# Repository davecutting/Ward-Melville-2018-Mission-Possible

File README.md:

# WMHS Mission Possible 2018 # 

This repository contains code and circuit board design files for Ward Melville High School's A team Mission Prossible device in the 2017-2018 season. All work represented here is the original work of David Cutting.

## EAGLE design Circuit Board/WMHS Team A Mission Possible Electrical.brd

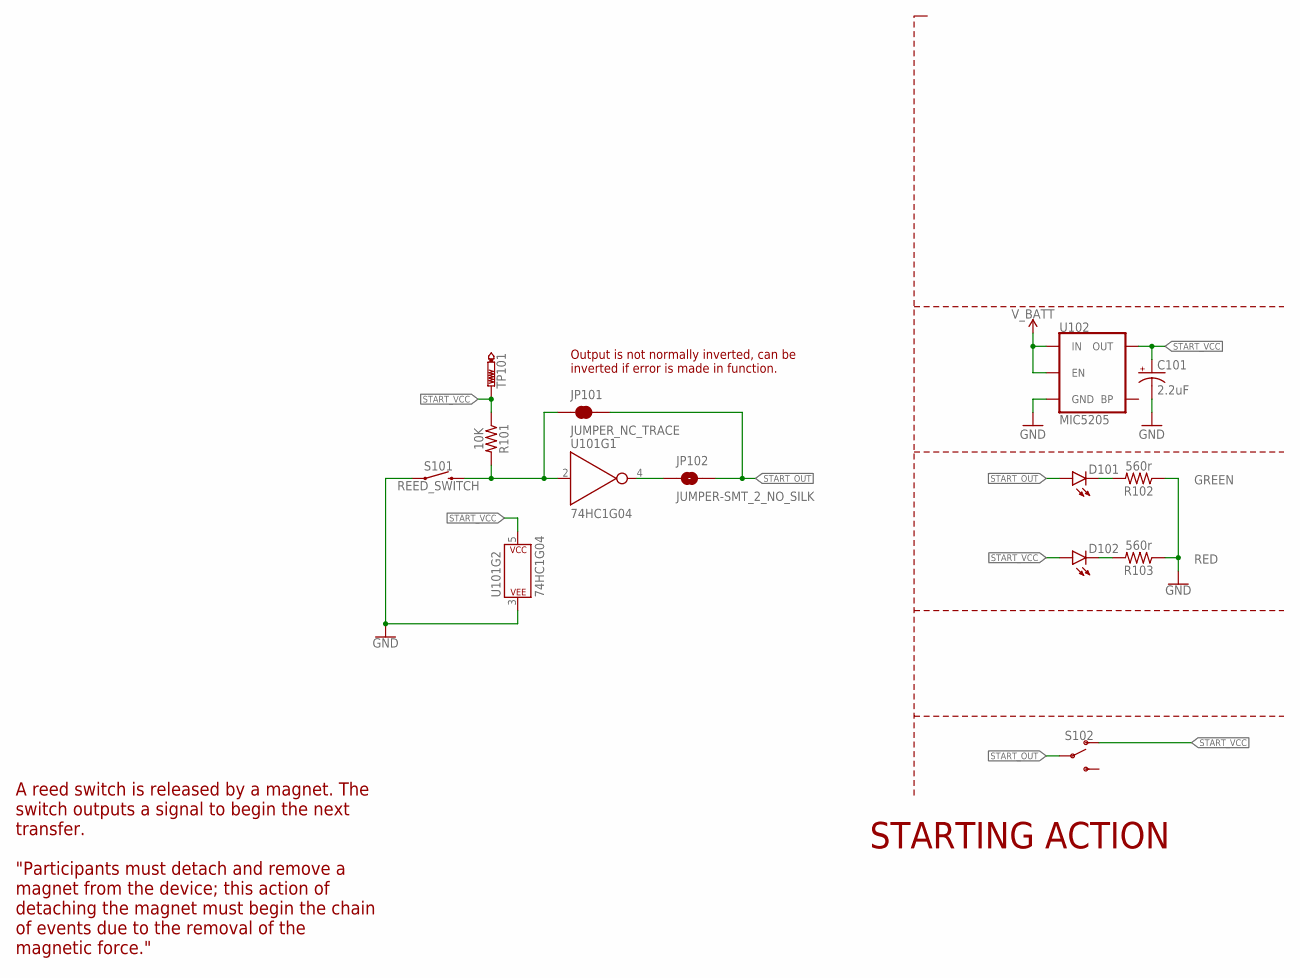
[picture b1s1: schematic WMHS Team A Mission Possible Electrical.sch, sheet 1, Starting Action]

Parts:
C101: 2.2uF; EIA3216
D101: GREEN; LED-0603
D102: RED; LED-0603
JP101: JUMPER_NC_TRACE; SMT-JUMPER_2_NC_TRACE_SILK
JP102: JUMPER-SMT_2_NO_SILK; SMT-JUMPER_2_NO_SILK
R101: 10K; 0603
R102, R103: 560r; 0603
S101: REED_SWITCH; AXIAL_GULLWING_REED
S102: SWITCH-SPDT-SMD-AYZ0202; SWITCH_DPDT_SMD_AYZ0202
TP101: PTR1TP20R; TP20R
U101: 74HC1G04; SOT353
U102: MIC5205; SOT23-5

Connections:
GND: C101.-, R102.1, R103.1, S101.P$1 (1), U101.3 (P$V-), U102.2 (GND); also elsewhere on the board
unnamed: JP102.1, U101.4 (Y)
unnamed: JP101.1, R101.2, S101.P$2 (2), U101.2 (A)
unnamed: D102.C, R103.2
unnamed: D101.C, R102.2
START_OUT: D101.A, JP101.2, JP102.2, S102.2; also elsewhere on the board
START_VCC: C101.+, D102.A, R101.1, S102.1 (O), TP101.TP, U101.5 (P$V+), U102.5 (OUT)
V_BATT: U102.1 (IN), U102.3 (EN); also elsewhere on the board

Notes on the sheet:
STARTING ACTION
"Participants must detach and remove a magnet from the device; this action of detaching the magnet must begin the chain of events due to the removal of the magnetic force."
A reed switch is released by a magnet. The switch outputs a signal to begin the next transfer.
Output is not normally inverted, can be inverted if error is made in function.

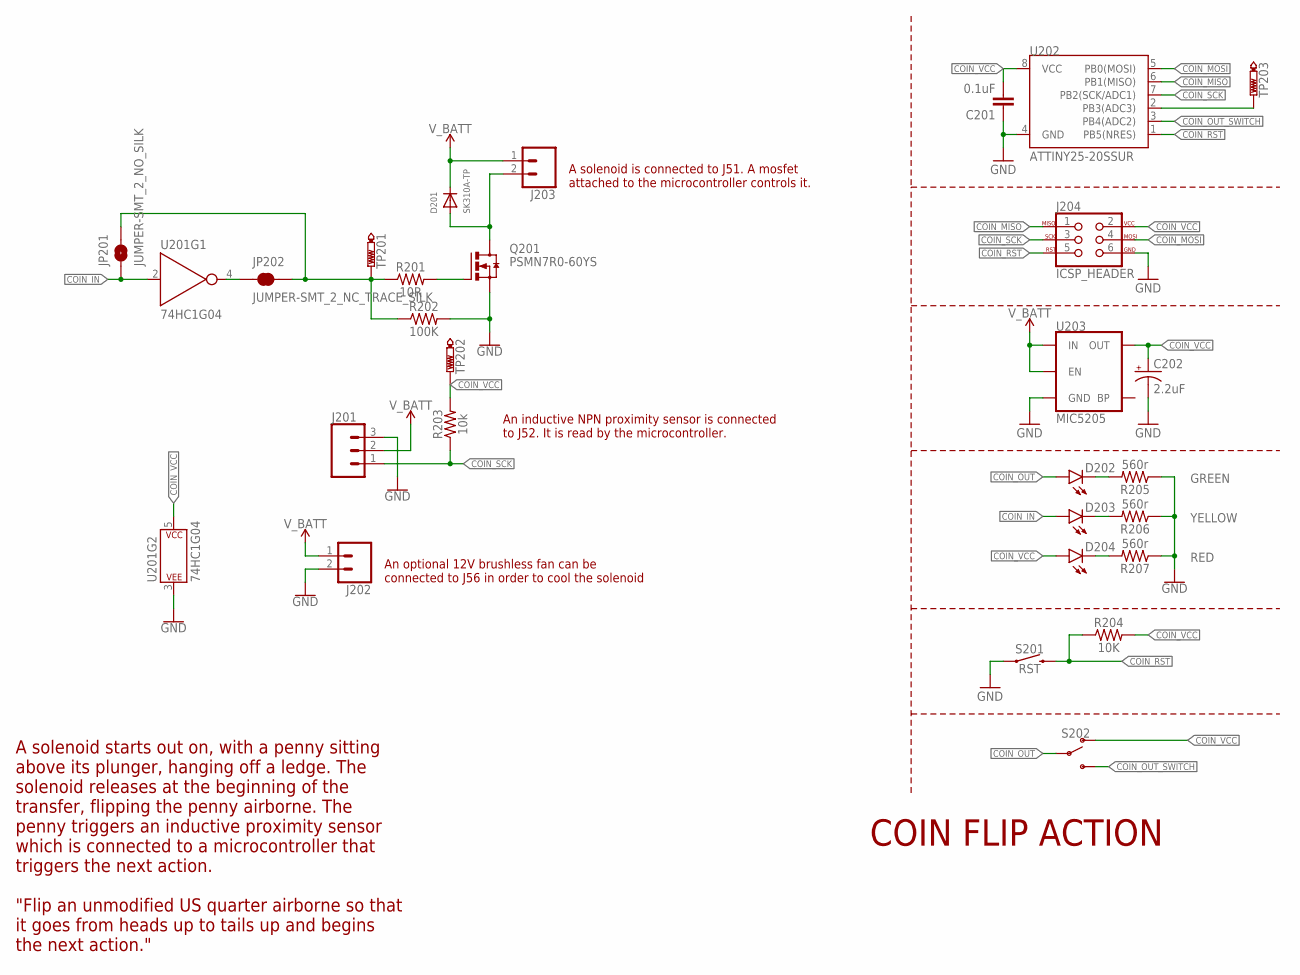
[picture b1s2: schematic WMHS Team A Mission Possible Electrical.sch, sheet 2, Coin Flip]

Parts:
C201: 0.1uF; 0603
C202: 2.2uF; EIA3216
D201: SK310A-TP; SMADIODE
D202: GREEN; LED-0603
D203: YELLOW; LED-0603
D204: RED; LED-0603
J201: CONN_03LOCK; 1X03_LOCK
J202: CONN_02LOCK; 1X02_LOCK
J203: CONN_023.5MM_LOCK; SCREWTERMINAL-3.5MM-2_LOCK
J204: ICSP_HEADER; 2X3
JP201: JUMPER-SMT_2_NO_SILK; SMT-JUMPER_2_NO_SILK
JP202: JUMPER-SMT_2_NC_TRACE_SILK; SMT-JUMPER_2_NC_TRACE_SILK
Q201: PSMN7R0-60YS; SOT669
R201: 10R; 0603
R202: 100K; 0603
R203: 10k; 0603
R204: 10K; 0603
R205, R206, R207: 560r; 0603
S201: RST; TACTILE_SWITCH_SMD_5.2MM
S202: SWITCH-SPDT-SMD-AYZ0202; SWITCH_DPDT_SMD_AYZ0202
TP201, TP202, TP203: PTR1TP20R; TP20R
U201: 74HC1G04; SOT353
U202: ATTINY25-20SSUR; SOIC8
U203: MIC5205; SOT23-5

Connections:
COIN_IN: D203.A, JP201.1, U201.2 (A); also elsewhere on the board
COIN_MISO: J204.1, U202.6 (PB1(MISO))
COIN_MOSI: J204.4, U202.5 (PB0(MOSI))
COIN_OUT: D202.A, S202.2; also elsewhere on the board
COIN_OUT_SWITCH: S202.3 (S), U202.3 (PB4(ADC2))
COIN_RST: J204.5, R204.1, S201.3 (2), S201.4 (2), U202.1 (PB5(NRES))
COIN_SCK: J201.1, J204.3, R203.1, U202.7 (PB2(SCK/ADC1))
COIN_VCC: C201.2, C202.+, D204.A, J204.2, R203.2, R204.2, S202.1 (O), TP202.TP, U201.5 (P$V+), U202.8 (VCC), U203.5 (OUT)
GND: C201.1, C202.-, J201.3, J202.2, J204.6, Q201.1 (S), Q201.2 (S), Q201.3 (S), R202.2, R205.1, R206.1, R207.1, S201.1, S201.2 (1), U201.3 (P$V-), U202.4 (GND), U203.2 (GND); also elsewhere on the board
unnamed: TP203.TP, U202.2 (PB3(ADC3))
unnamed: JP201.2, JP202.2, R201.1, R202.1, TP201.TP
unnamed: JP202.1, U201.4 (Y)
unnamed: Q201.4 (G), R201.2
unnamed: D201.A, J203.2, Q201.MB (D)
unnamed: D204.C, R207.2
unnamed: D203.C, R206.2
unnamed: D202.C, R205.2
V_BATT: D201.C, J201.2, J202.1, J203.1, U203.1 (IN), U203.3 (EN); also elsewhere on the board

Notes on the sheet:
COIN FLIP ACTION
"Flip an unmodified US quarter airborne so that it goes from heads up to tails up and begins the next action."
A solenoid is connected to J51. A mosfet attached to the microcontroller controls it.
An inductive NPN proximity sensor is connected to J52. It is read by the microcontroller.
An optional 12V brushless fan can be connected to J56 in order to cool the solenoid
A solenoid starts out on, with a penny sitting above its plunger, hanging off a ledge. The solenoid releases at the beginning of the transfer, flipping the penny airborne. The penny triggers an inductive proximity sensor which is connected to a microcontroller that triggers the next action.

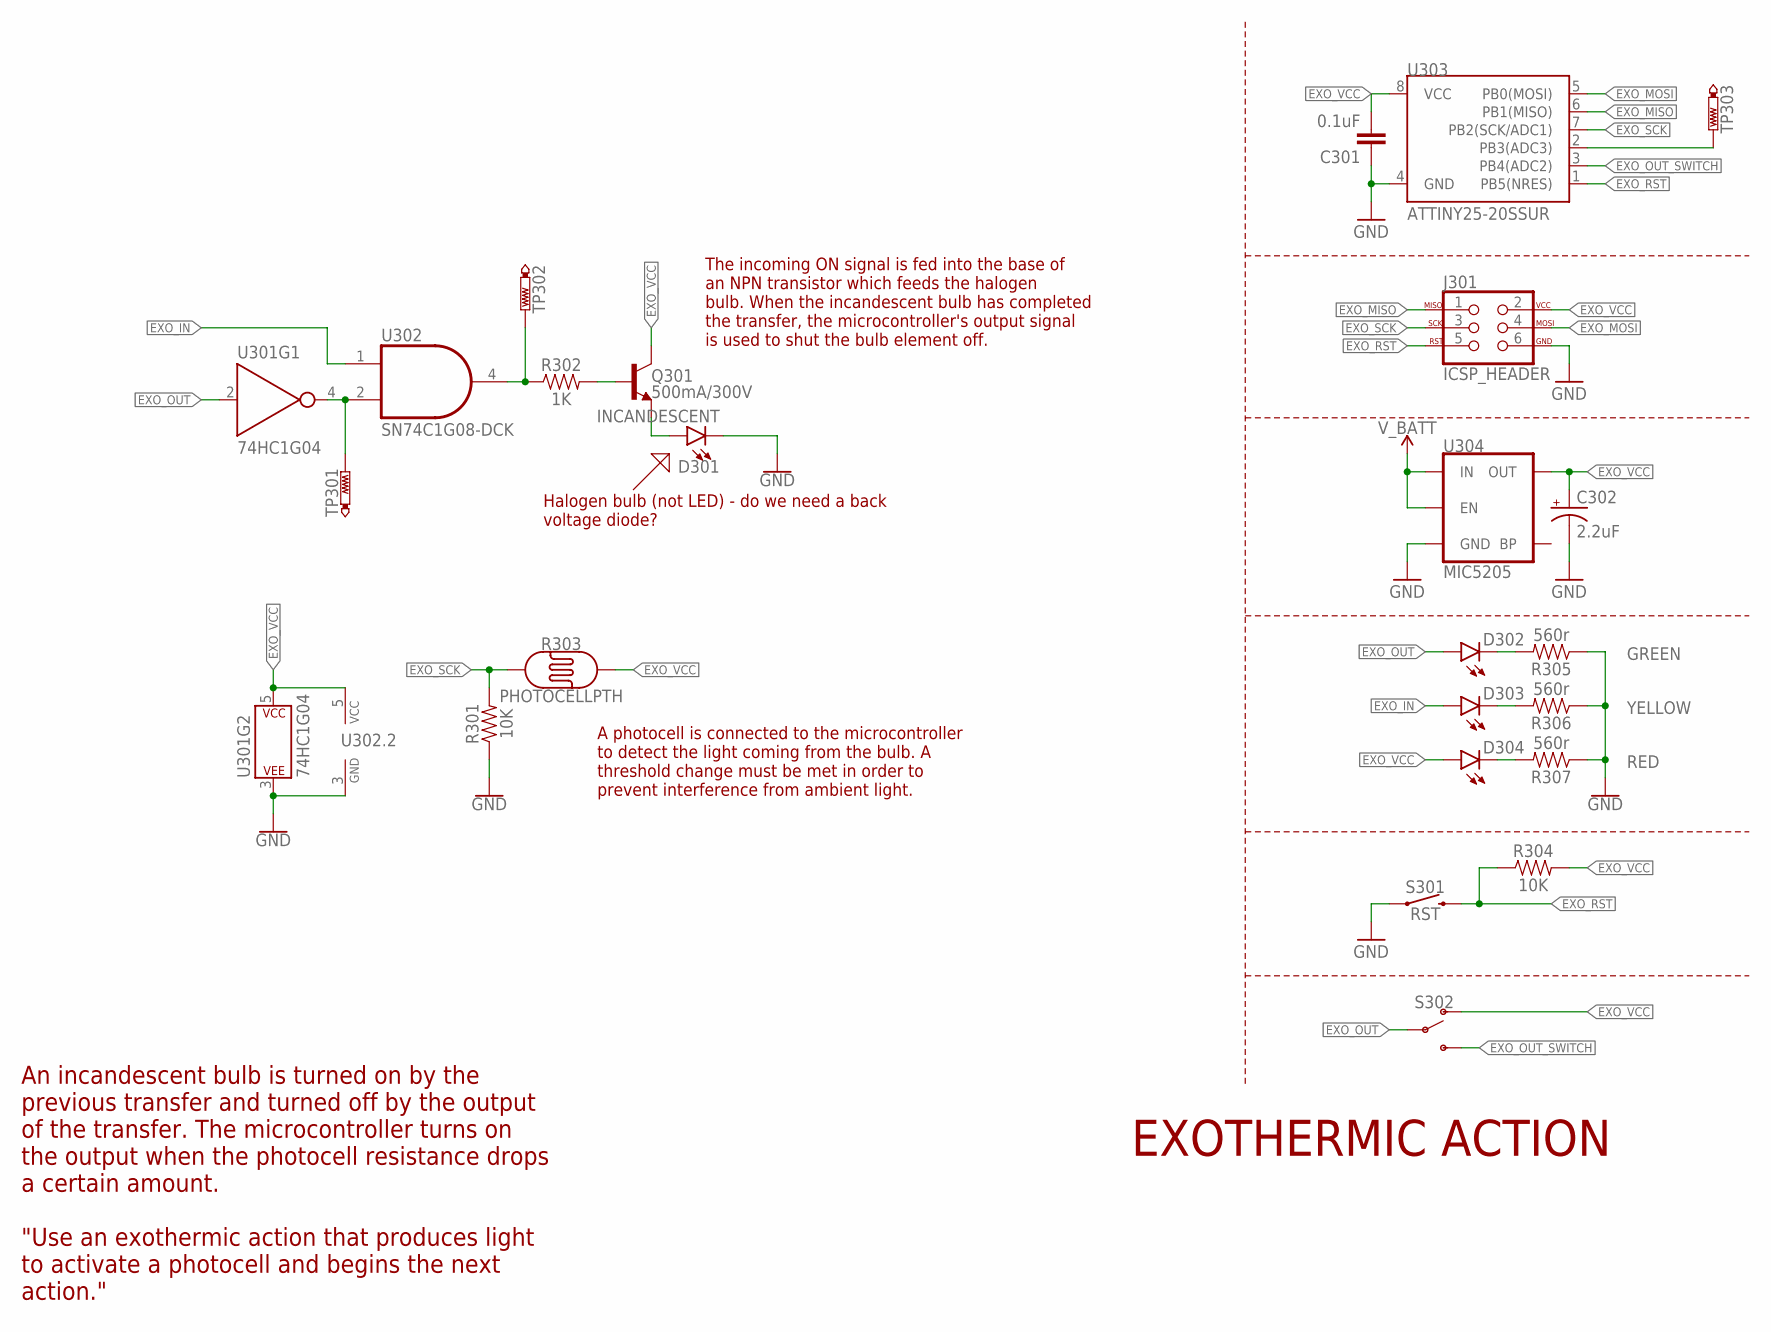
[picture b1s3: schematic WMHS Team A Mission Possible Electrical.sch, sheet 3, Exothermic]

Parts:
C301: 0.1uF; 0603
C302: 2.2uF; EIA3216
D301: INCANDESCENT; LED_3MM
D302: GREEN; LED-0603
D303: YELLOW; LED-0603
D304: RED; LED-0603
J301: ICSP_HEADER; 2X3
Q301: 500mA/300V; SOT23-3
R301, R304: 10K; 0603
R302: 1K; 0603
R303: PHOTOCELLPTH; PHOTOCELL
R305, R306, R307: 560r; 0603
S301: RST; TACTILE_SWITCH_SMD_5.2MM
S302: SWITCH-SPDT-SMD-AYZ0202; SWITCH_DPDT_SMD_AYZ0202
TP301, TP302, TP303: PTR1TP20R; TP20R
U301: 74HC1G04; SOT353
U302: SN74C1G08-DCK; SC-70-5
U303: ATTINY25-20SSUR; SOIC8
U304: MIC5205; SOT23-5

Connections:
EXO_IN: D303.A, U302.1 (A); also elsewhere on the board
EXO_MISO: J301.1, U303.6 (PB1(MISO))
EXO_MOSI: J301.4, U303.5 (PB0(MOSI))
EXO_OUT: D302.A, S302.2, U301.2 (A); also elsewhere on the board
EXO_OUT_SWITCH: S302.3 (S), U303.3 (PB4(ADC2))
EXO_RST: J301.5, R304.1, S301.3 (2), S301.4 (2), U303.1 (PB5(NRES))
EXO_SCK: J301.3, R301.2, R303.1, U303.7 (PB2(SCK/ADC1))
EXO_VCC: C301.2, C302.+, D304.A, J301.2, Q301.3 (C), R303.2, R304.2, S302.1 (O), U301.5 (P$V+), U302.5 (VCC), U303.8 (VCC), U304.5 (OUT)
GND: C301.1, C302.-, D301.K (C), J301.6, R301.1, R305.1, R306.1, R307.1, S301.1, S301.2 (1), U301.3 (P$V-), U302.3 (GND), U303.4 (GND), U304.2 (GND); also elsewhere on the board
unnamed: R302.1, TP302.TP, U302.4 (Y)
unnamed: TP301.TP, U301.4 (Y), U302.2 (B)
unnamed: TP303.TP, U303.2 (PB3(ADC3))
unnamed: Q301.1 (B), R302.2
unnamed: D301.A, Q301.2 (E)
unnamed: D304.C, R307.2
unnamed: D303.C, R306.2
unnamed: D302.C, R305.2
V_BATT: U304.1 (IN), U304.3 (EN); also elsewhere on the board

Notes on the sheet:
EXOTHERMIC ACTION
"Use an exothermic action that produces light to activate a photocell and begins the next action."
Halogen bulb (not LED) - do we need a back voltage diode?
The incoming ON signal is fed into the base of an NPN transistor which feeds the halogen bulb. When the incandescent bulb has completed the transfer, the microcontroller's output signal is used to shut the bulb element off.
A photocell is connected to the microcontroller to detect the light coming from the bulb. A threshold change must be met in order to prevent interference from ambient light.
An incandescent bulb is turned on by the previous transfer and turned off by the output of the transfer. The microcontroller turns on the output when the photocell resistance drops a certain amount.

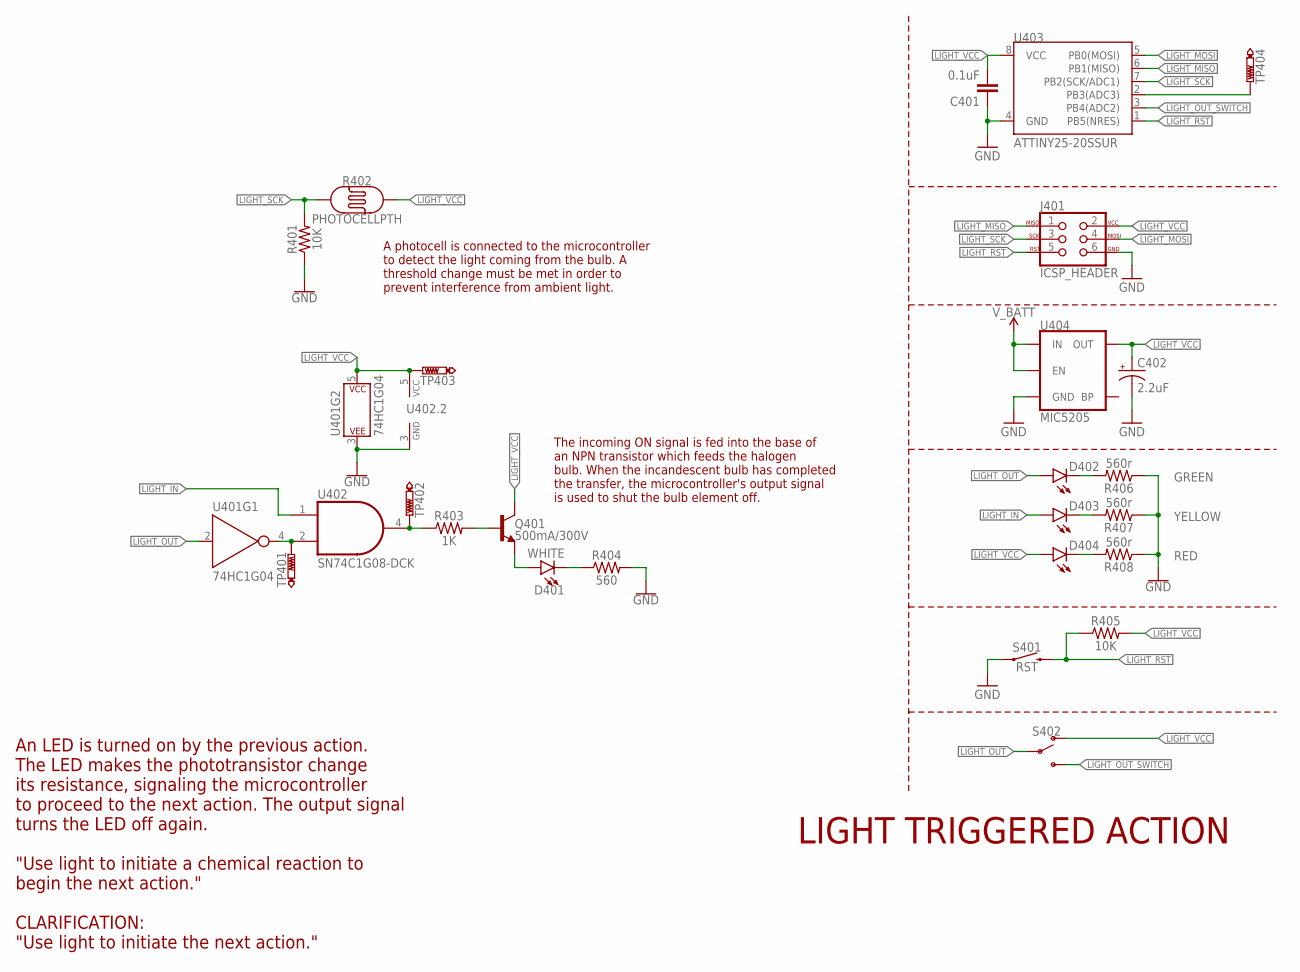
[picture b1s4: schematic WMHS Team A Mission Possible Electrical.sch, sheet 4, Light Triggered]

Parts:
C401: 0.1uF; 0603
C402: 2.2uF; EIA3216
D401: WHITE; LED_3MM
D402: GREEN; LED-0603
D403: YELLOW; LED-0603
D404: RED; LED-0603
J401: ICSP_HEADER; 2X3
Q401: 500mA/300V; SOT23-3
R401, R405: 10K; 0603
R402: PHOTOCELLPTH; PHOTOCELL
R403: 1K; 0603
R404: 560; 0603
R406, R407, R408: 560r; 0603
S401: RST; TACTILE_SWITCH_SMD_5.2MM
S402: SWITCH-SPDT-SMD-AYZ0202; SWITCH_DPDT_SMD_AYZ0202
TP401, TP402, TP403, TP404: PTR1TP20R; TP20R
U401: 74HC1G04; SOT353
U402: SN74C1G08-DCK; SC-70-5
U403: ATTINY25-20SSUR; SOIC8
U404: MIC5205; SOT23-5

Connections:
GND: C401.1, C402.-, J401.6, R401.1, R404.2, R406.1, R407.1, R408.1, S401.1, S401.2 (1), U401.3 (P$V-), U402.3 (GND), U403.4 (GND), U404.2 (GND); also elsewhere on the board
LIGHT_IN: D403.A, U402.1 (A); also elsewhere on the board
LIGHT_MISO: J401.1, U403.6 (PB1(MISO))
LIGHT_MOSI: J401.4, U403.5 (PB0(MOSI))
LIGHT_OUT: D402.A, S402.2, U401.2 (A); also elsewhere on the board
LIGHT_OUT_SWITCH: S402.3 (S), U403.3 (PB4(ADC2))
LIGHT_RST: J401.5, R405.1, S401.3 (2), S401.4 (2), U403.1 (PB5(NRES))
LIGHT_SCK: J401.3, R401.2, R402.1, U403.7 (PB2(SCK/ADC1))
LIGHT_VCC: C401.2, C402.+, D404.A, J401.2, Q401.3 (C), R402.2, R405.2, S402.1 (O), TP403.TP, U401.5 (P$V+), U402.5 (VCC), U403.8 (VCC), U404.5 (OUT)
unnamed: Q401.1 (B), R403.2
unnamed: D401.A, Q401.2 (E)
unnamed: R403.1, TP402.TP, U402.4 (Y)
unnamed: TP401.TP, U401.4 (Y), U402.2 (B)
unnamed: TP404.TP, U403.2 (PB3(ADC3))
unnamed: D401.K (C), R404.1
unnamed: D404.C, R408.2
unnamed: D403.C, R407.2
unnamed: D402.C, R406.2
V_BATT: U404.1 (IN), U404.3 (EN); also elsewhere on the board

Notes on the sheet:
LIGHT TRIGGERED ACTION
"Use light to initiate a chemical reaction to begin the next action." CLARIFICATION: "Use light to initiate the next action."
An LED is turned on by the previous action. The LED makes the phototransistor change its resistance, signaling the microcontroller to proceed to the next action. The output signal turns the LED off again.
A photocell is connected to the microcontroller to detect the light coming from the bulb. A threshold change must be met in order to prevent interference from ambient light.
The incoming ON signal is fed into the base of an NPN transistor which feeds the halogen bulb. When the incandescent bulb has completed the transfer, the microcontroller's output signal is used to shut the bulb element off.

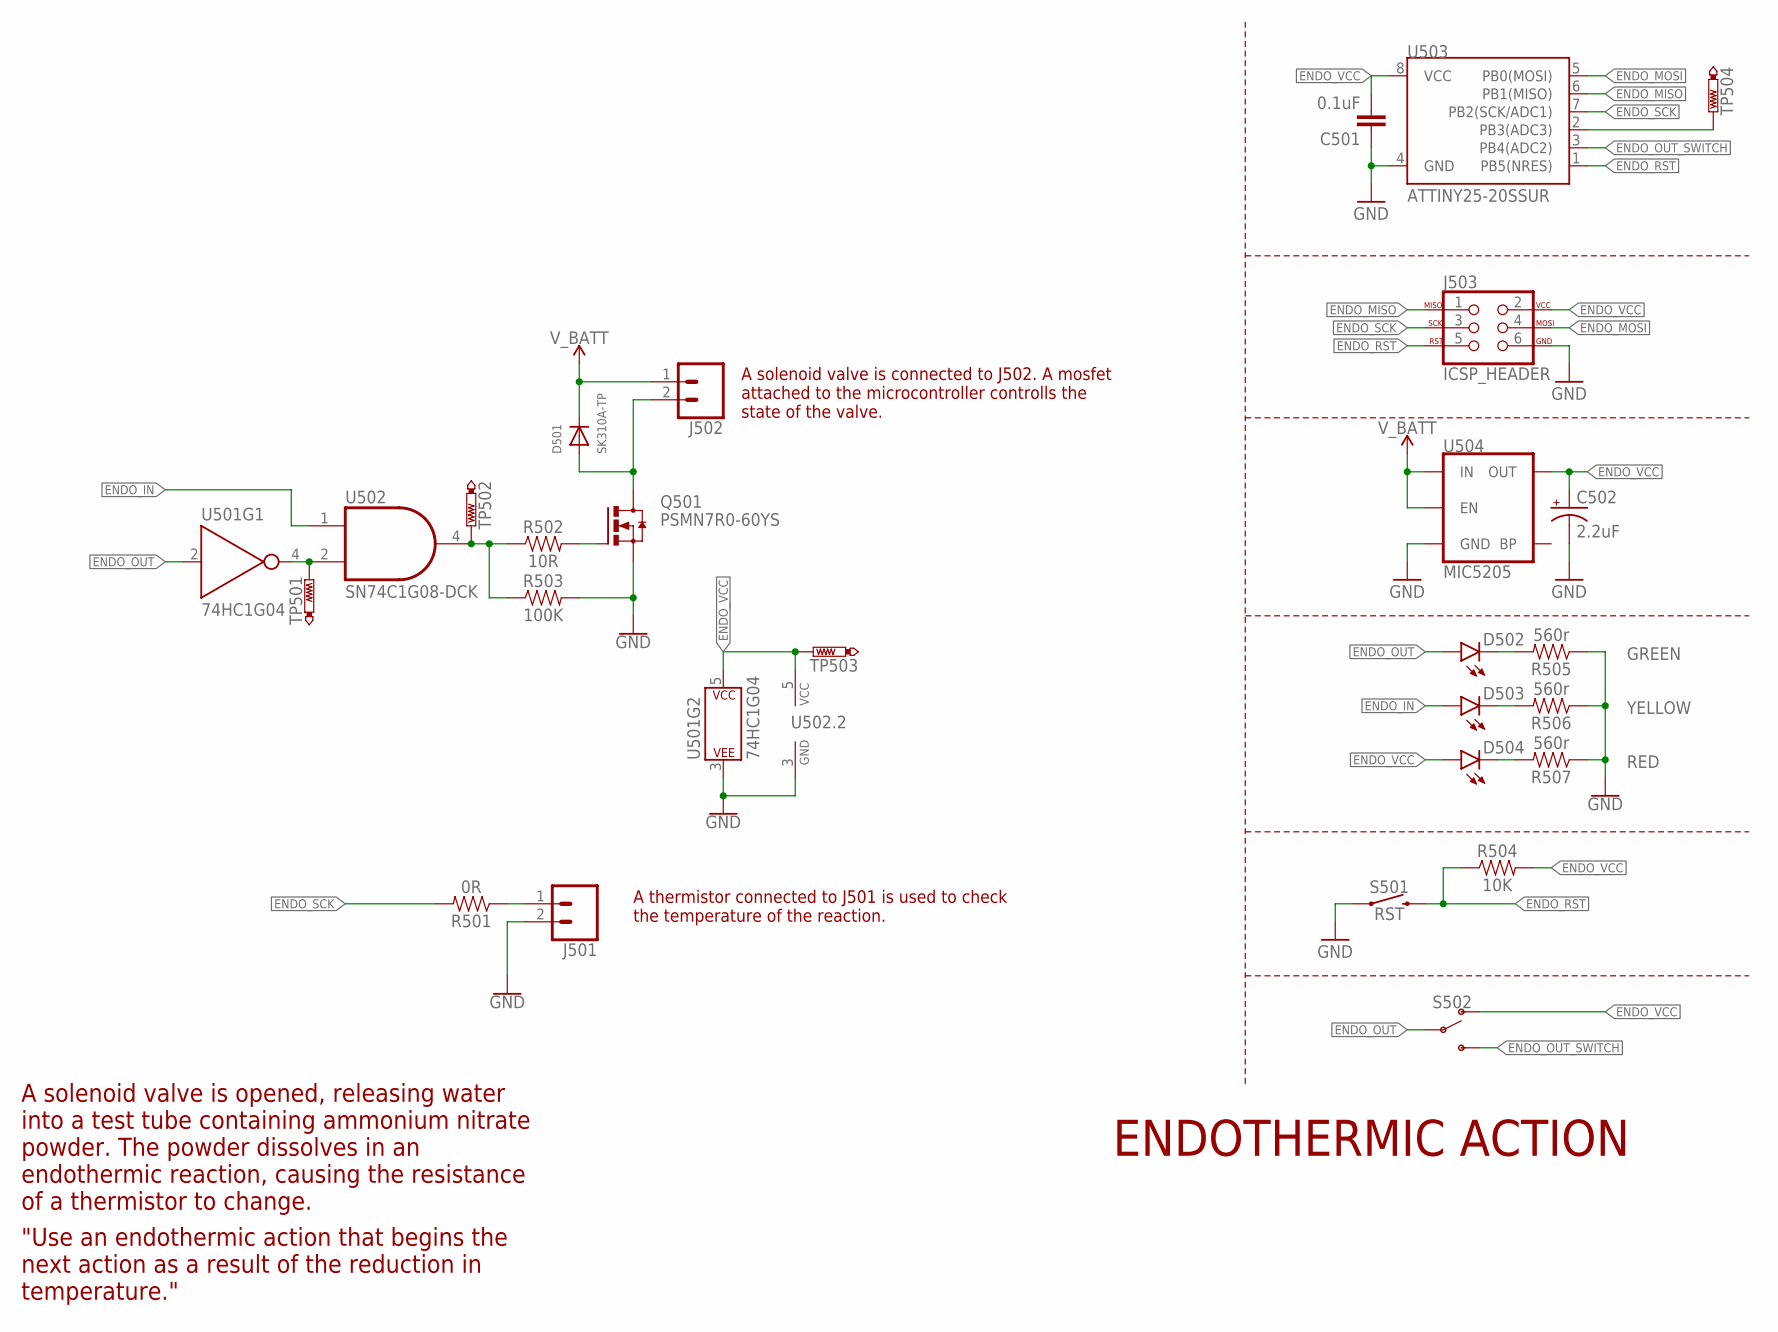
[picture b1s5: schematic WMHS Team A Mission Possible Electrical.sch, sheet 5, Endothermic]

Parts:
C501: 0.1uF; 0603
C502: 2.2uF; EIA3216
D501: SK310A-TP; SMADIODE
D502: GREEN; LED-0603
D503: YELLOW; LED-0603
D504: RED; LED-0603
J501: CONN_02LOCK; 1X02_LOCK
J502: CONN_023.5MM_LOCK; SCREWTERMINAL-3.5MM-2_LOCK
J503: ICSP_HEADER; 2X3
Q501: PSMN7R0-60YS; SOT669
R501: 0R; 0603
R502: 10R; 0603
R503: 100K; 0603
R504: 10K; 0603
R505, R506, R507: 560r; 0603
S501: RST; TACTILE_SWITCH_SMD_5.2MM
S502: SWITCH-SPDT-SMD-AYZ0202; SWITCH_DPDT_SMD_AYZ0202
TP501, TP502, TP503, TP504: PTR1TP20R; TP20R
U501: 74HC1G04; SOT353
U502: SN74C1G08-DCK; SC-70-5
U503: ATTINY25-20SSUR; SOIC8
U504: MIC5205; SOT23-5

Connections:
ENDO_IN: D503.A, U502.1 (A); also elsewhere on the board
ENDO_MISO: J503.1, U503.6 (PB1(MISO))
ENDO_MOSI: J503.4, U503.5 (PB0(MOSI))
ENDO_OUT: D502.A, S502.2, U501.2 (A); also elsewhere on the board
ENDO_OUT_SWITCH: S502.3 (S), U503.3 (PB4(ADC2))
ENDO_RST: J503.5, R504.1, S501.3 (2), S501.4 (2), U503.1 (PB5(NRES))
ENDO_SCK: J503.3, R501.2, U503.7 (PB2(SCK/ADC1))
ENDO_VCC: C501.2, C502.+, D504.A, J503.2, R504.2, S502.1 (O), TP503.TP, U501.5 (P$V+), U502.5 (VCC), U503.8 (VCC), U504.5 (OUT)
GND: C501.1, C502.-, J501.2, J503.6, Q501.1 (S), Q501.2 (S), Q501.3 (S), R503.2, R505.1, R506.1, R507.1, S501.1, S501.2 (1), U501.3 (P$V-), U502.3 (GND), U503.4 (GND), U504.2 (GND); also elsewhere on the board
unnamed: TP501.TP, U501.4 (Y), U502.2 (B)
unnamed: TP504.TP, U503.2 (PB3(ADC3))
unnamed: J501.1, R501.1
unnamed: Q501.4 (G), R502.2
unnamed: D501.A, J502.2, Q501.MB (D)
unnamed: R502.1, R503.1, TP502.TP, U502.4 (Y)
unnamed: D504.C, R507.2
unnamed: D503.C, R506.2
unnamed: D502.C, R505.2
V_BATT: D501.C, J502.1, U504.1 (IN), U504.3 (EN); also elsewhere on the board

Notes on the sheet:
ENDOTHERMIC ACTION
"Use an endothermic action that begins the next action as a result of the reduction in temperature."
A thermistor connected to J501 is used to check the temperature of the reaction.
A solenoid valve is connected to J502. A mosfet attached to the microcontroller controlls the state of the valve.
A solenoid valve is opened, releasing water into a test tube containing ammonium nitrate powder. The powder dissolves in an endothermic reaction, causing the resistance of a thermistor to change.

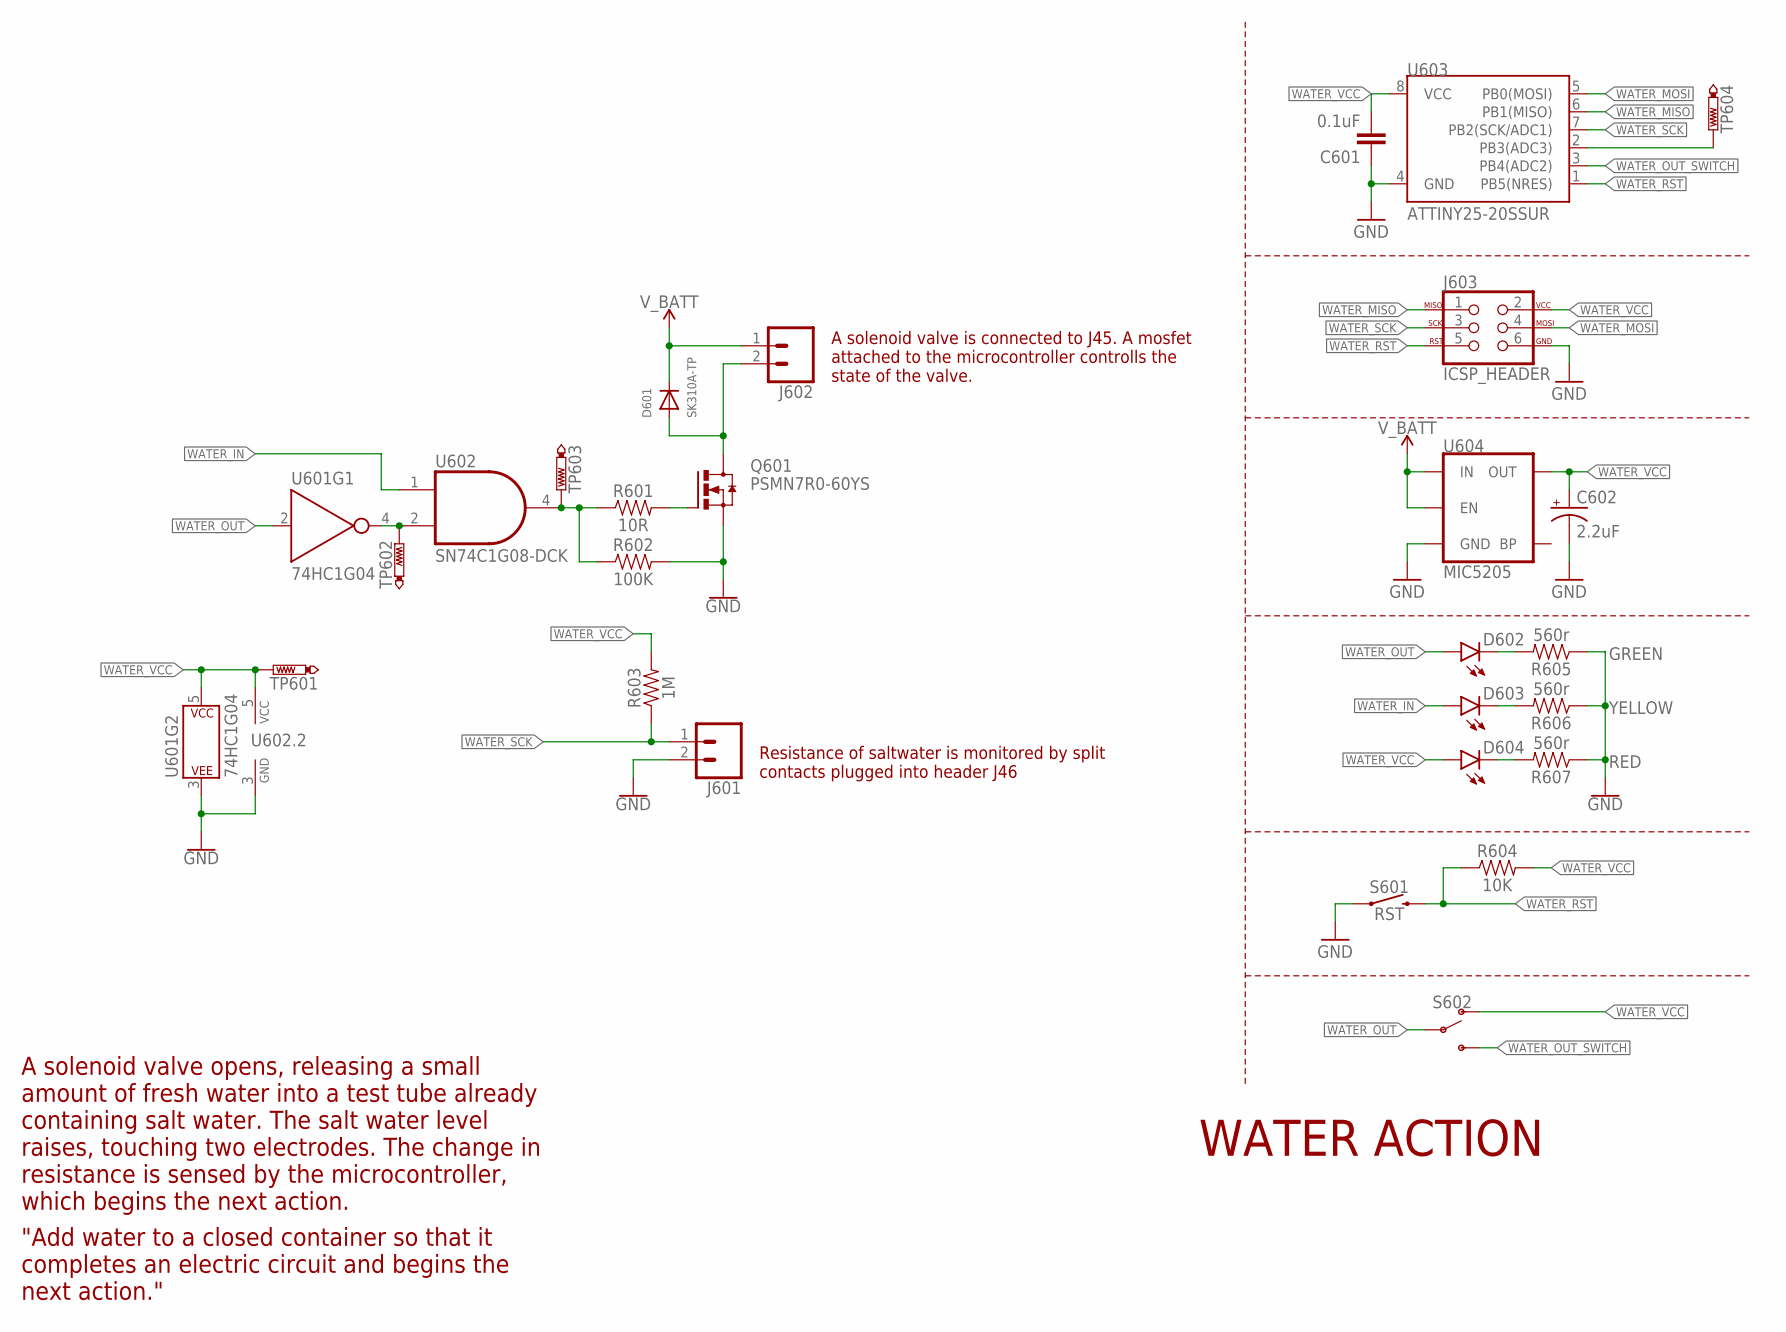
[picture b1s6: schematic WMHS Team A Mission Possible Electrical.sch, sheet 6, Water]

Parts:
C601: 0.1uF; 0603
C602: 2.2uF; EIA3216
D601: SK310A-TP; SMADIODE
D602: GREEN; LED-0603
D603: YELLOW; LED-0603
D604: RED; LED-0603
J601: CONN_02LOCK; 1X02_LOCK
J602: CONN_023.5MM_LOCK; SCREWTERMINAL-3.5MM-2_LOCK
J603: ICSP_HEADER; 2X3
Q601: PSMN7R0-60YS; SOT669
R601: 10R; 0603
R602: 100K; 0603
R603: 1M; 0603
R604: 10K; 0603
R605, R606, R607: 560r; 0603
S601: RST; TACTILE_SWITCH_SMD_5.2MM
S602: SWITCH-SPDT-SMD-AYZ0202; SWITCH_DPDT_SMD_AYZ0202
TP601, TP602, TP603, TP604: PTR1TP20R; TP20R
U601: 74HC1G04; SOT353
U602: SN74C1G08-DCK; SC-70-5
U603: ATTINY25-20SSUR; SOIC8
U604: MIC5205; SOT23-5

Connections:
GND: C601.1, C602.-, J601.2, J603.6, Q601.1 (S), Q601.2 (S), Q601.3 (S), R602.2, R605.1, R606.1, R607.1, S601.1, S601.2 (1), U601.3 (P$V-), U602.3 (GND), U603.4 (GND), U604.2 (GND); also elsewhere on the board
unnamed: TP602.TP, U601.4 (Y), U602.2 (B)
unnamed: TP604.TP, U603.2 (PB3(ADC3))
unnamed: D604.C, R607.2
unnamed: D603.C, R606.2
unnamed: D602.C, R605.2
unnamed: R601.1, R602.1, TP603.TP, U602.4 (Y)
unnamed: Q601.4 (G), R601.2
unnamed: D601.A, J602.2, Q601.MB (D)
V_BATT: D601.C, J602.1, U604.1 (IN), U604.3 (EN); also elsewhere on the board
WATER_IN: D603.A, U602.1 (A); also elsewhere on the board
WATER_MISO: J603.1, U603.6 (PB1(MISO))
WATER_MOSI: J603.4, U603.5 (PB0(MOSI))
WATER_OUT: D602.A, S602.2, U601.2 (A); also elsewhere on the board
WATER_OUT_SWITCH: S602.3 (S), U603.3 (PB4(ADC2))
WATER_RST: J603.5, R604.1, S601.3 (2), S601.4 (2), U603.1 (PB5(NRES))
WATER_SCK: J601.1, J603.3, R603.1, U603.7 (PB2(SCK/ADC1))
WATER_VCC: C601.2, C602.+, D604.A, J603.2, R603.2, R604.2, S602.1 (O), TP601.TP, U601.5 (P$V+), U602.5 (VCC), U603.8 (VCC), U604.5 (OUT)

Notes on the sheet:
WATER ACTION
"Add water to a closed container so that it completes an electric circuit and begins the next action."
A solenoid valve is connected to J45. A mosfet attached to the microcontroller controlls the state of the valve.
Resistance of saltwater is monitored by split contacts plugged into header J46
A solenoid valve opens, releasing a small amount of fresh water into a test tube already containing salt water. The salt water level raises, touching two electrodes. The change in resistance is sensed by the microcontroller, which begins the next action.

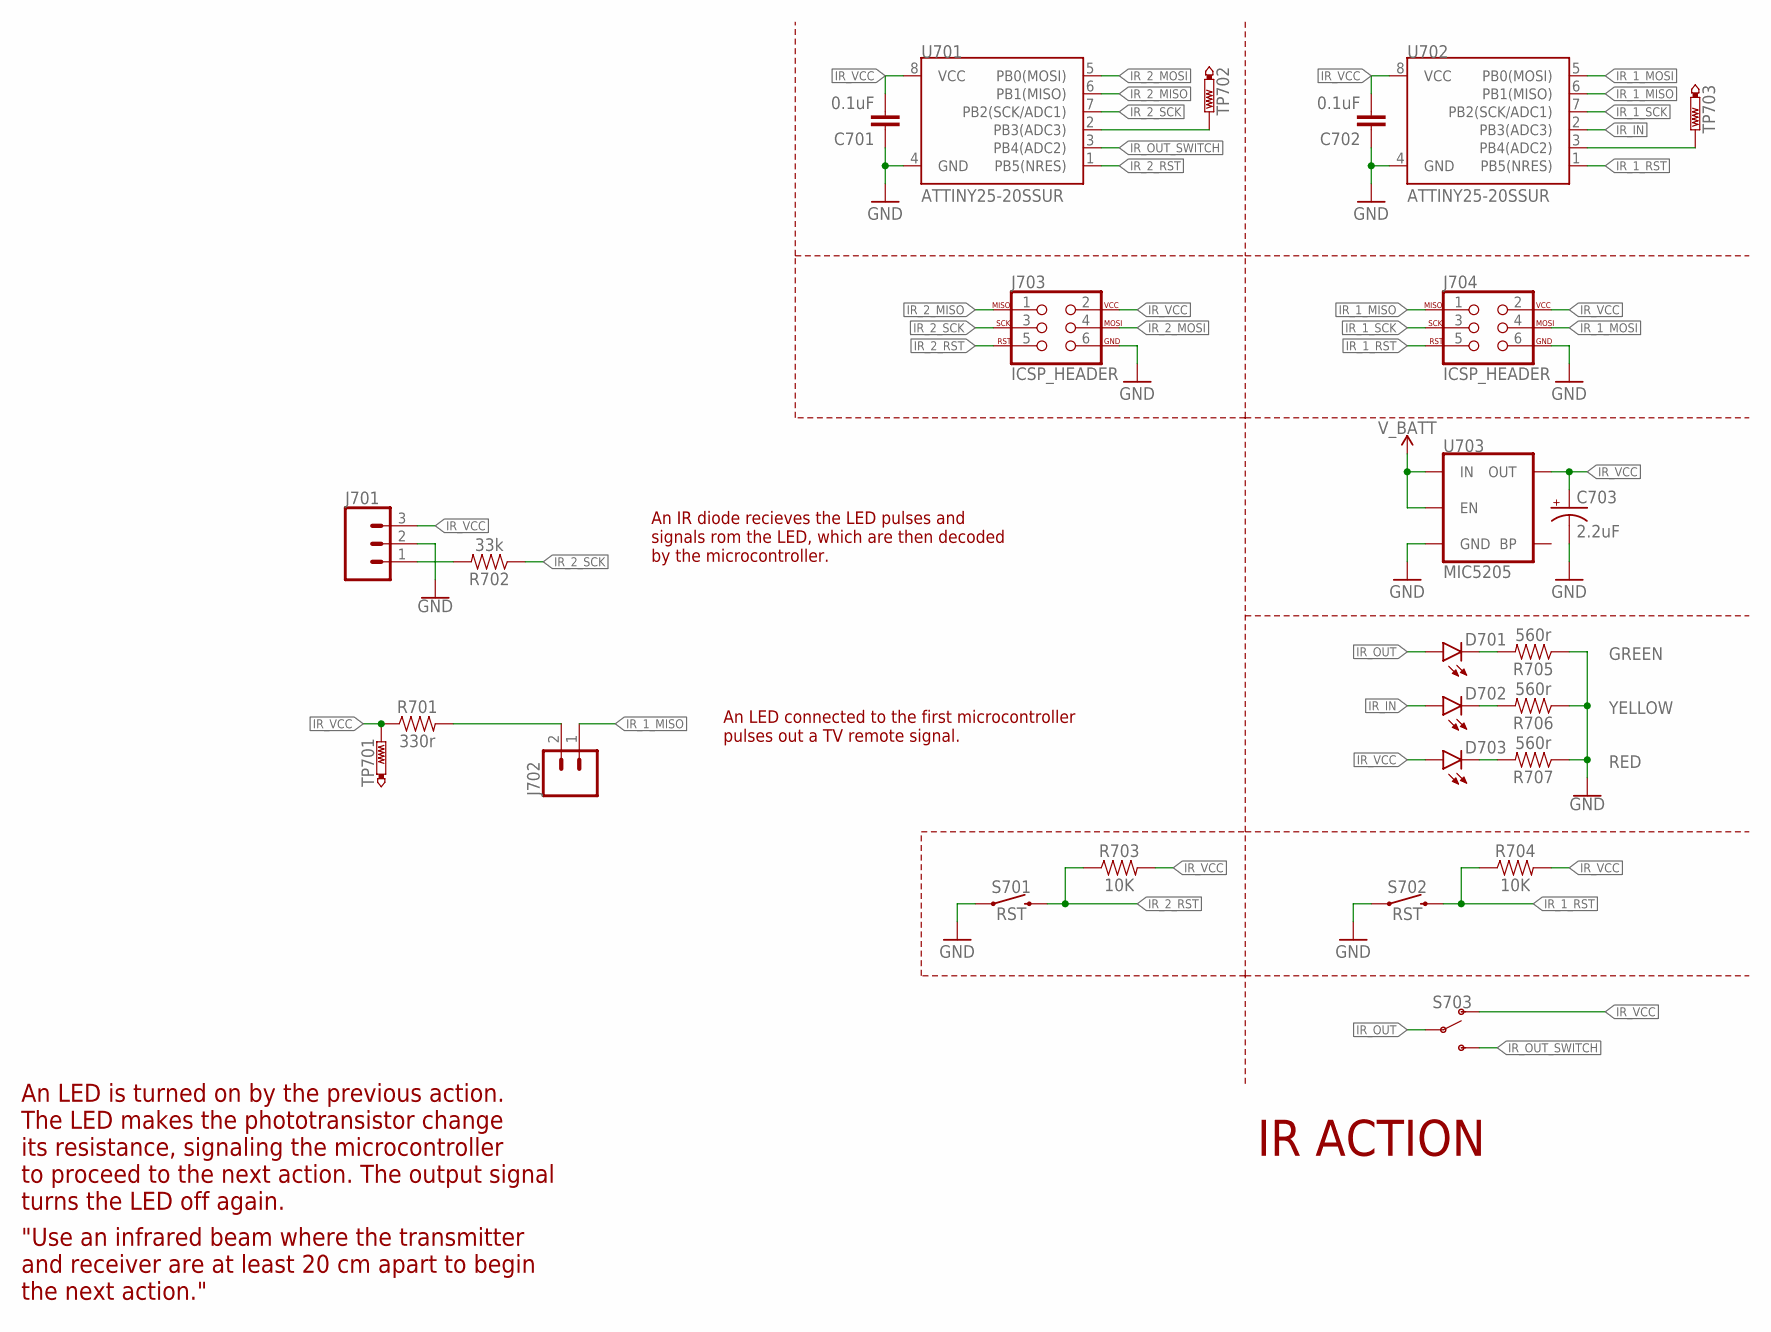
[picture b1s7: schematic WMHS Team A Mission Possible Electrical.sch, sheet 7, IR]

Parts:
C701, C702: 0.1uF; 0603
C703: 2.2uF; EIA3216
D701: GREEN; LED-0603
D702: YELLOW; LED-0603
D703: RED; LED-0603
J701: CONN_03; 1X03
J702: CONN_02LOCK; 1X02_LOCK
J703, J704: ICSP_HEADER; 2X3
R701: 330r; 0603
R702: 33k; 0603
R703, R704: 10K; 0603
R705, R706, R707: 560r; 0603
S701, S702: RST; TACTILE_SWITCH_SMD_5.2MM
S703: SWITCH-SPDT-SMD-AYZ0202; SWITCH_DPDT_SMD_AYZ0202
TP701, TP702, TP703: PTR1TP20R; TP20R
U701, U702: ATTINY25-20SSUR; SOIC8
U703: MIC5205; SOT23-5

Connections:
GND: C701.1, C702.1, C703.-, J701.2, J703.6, J704.6, R705.1, R706.1, R707.1, S701.1, S701.2 (1), S702.1, S702.2 (1), U701.4 (GND), U702.4 (GND), U703.2 (GND); also elsewhere on the board
IR_1_MISO: J702.1, J704.1, U702.6 (PB1(MISO))
IR_1_MOSI: J704.4, U702.5 (PB0(MOSI))
IR_1_RST: J704.5, R704.1, S702.3 (2), S702.4 (2), U702.1 (PB5(NRES))
IR_1_SCK: J704.3, U702.7 (PB2(SCK/ADC1))
IR_2_MISO: J703.1, U701.6 (PB1(MISO))
IR_2_MOSI: J703.4, U701.5 (PB0(MOSI))
IR_2_RST: J703.5, R703.1, S701.3 (2), S701.4 (2), U701.1 (PB5(NRES))
IR_2_SCK: J703.3, R702.1, U701.7 (PB2(SCK/ADC1))
IR_IN: D702.A, U702.2 (PB3(ADC3)); also elsewhere on the board
IR_OUT: D701.A, S703.2; also elsewhere on the board
IR_OUT_SWITCH: S703.3 (S), U701.3 (PB4(ADC2))
IR_VCC: C701.2, C702.2, C703.+, D703.A, J701.3, J703.2, J704.2, R701.1, R703.2, R704.2, S703.1 (O), TP701.TP, U701.8 (VCC), U702.8 (VCC), U703.5 (OUT)
unnamed: TP702.TP, U701.2 (PB3(ADC3))
unnamed: TP703.TP, U702.3 (PB4(ADC2))
unnamed: D703.C, R707.2
unnamed: J702.2, R701.2
unnamed: J701.1, R702.2
unnamed: D702.C, R706.2
unnamed: D701.C, R705.2
V_BATT: U703.1 (IN), U703.3 (EN); also elsewhere on the board

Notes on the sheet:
IR ACTION
"Use an infrared beam where the transmitter and receiver are at least 20 cm apart to begin the next action."
An IR diode recieves the LED pulses and signals rom the LED, which are then decoded by the microcontroller.
An LED connected to the first microcontroller pulses out a TV remote signal.
An LED is turned on by the previous action. The LED makes the phototransistor change its resistance, signaling the microcontroller to proceed to the next action. The output signal turns the LED off again.

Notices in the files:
parts and their libraries:
SparkFun-Capacitors: Licensing: Creative Commons ShareAlike 4.0 International - https://creativecommons.org/licenses/by-sa/4.0
m-pad-2.1: License : GNU General Public License version 2 (see bottom)
